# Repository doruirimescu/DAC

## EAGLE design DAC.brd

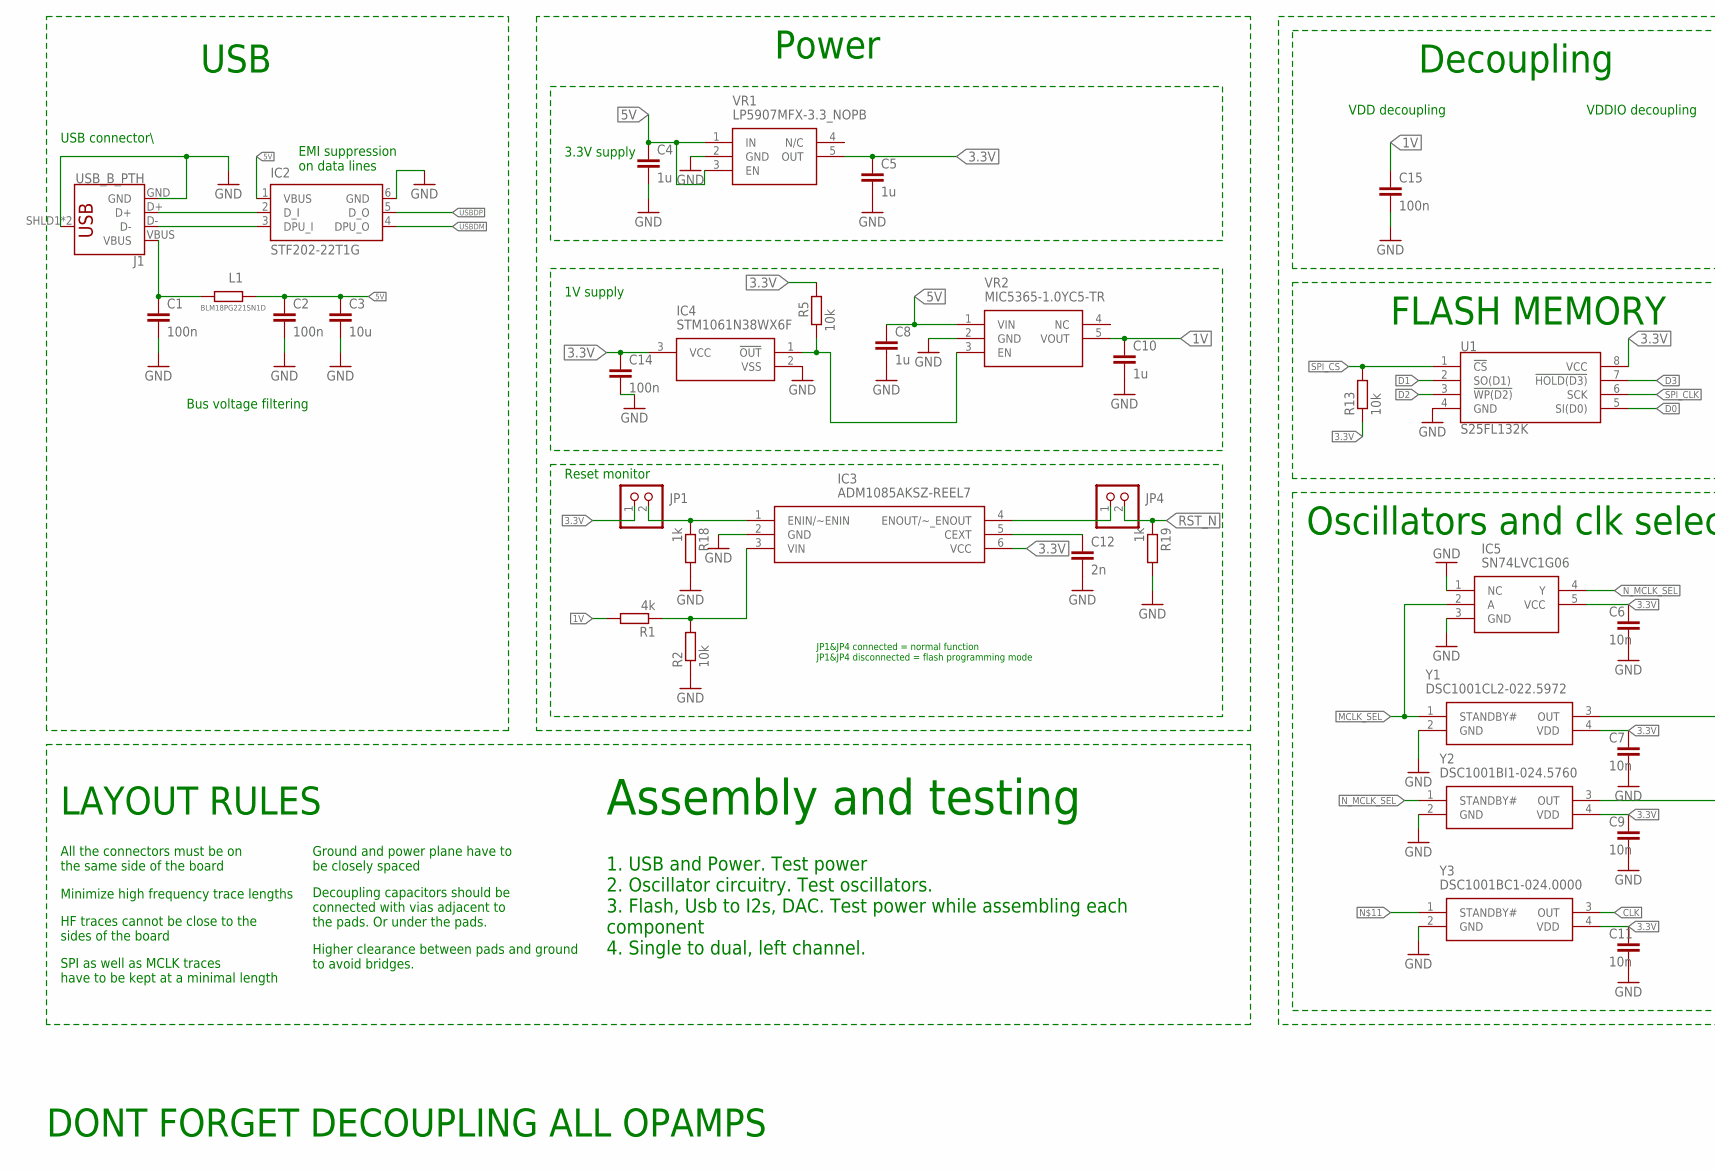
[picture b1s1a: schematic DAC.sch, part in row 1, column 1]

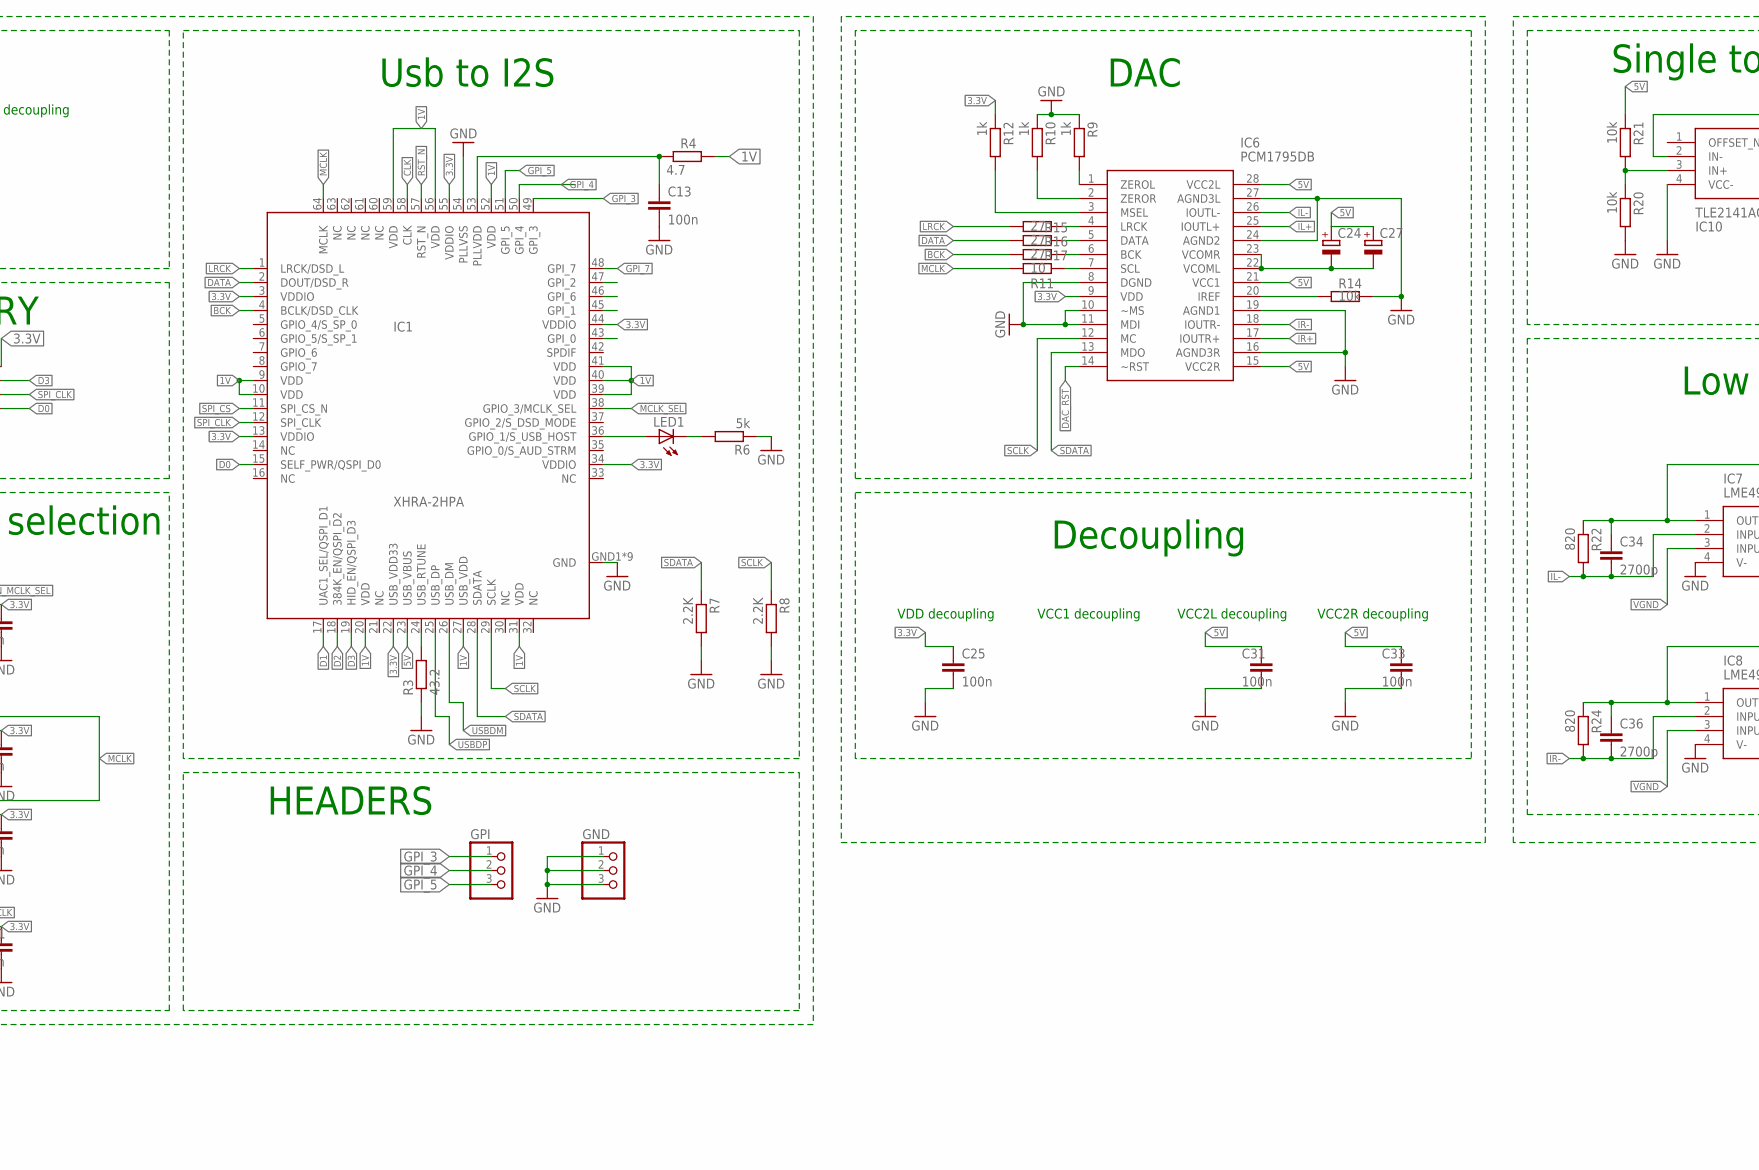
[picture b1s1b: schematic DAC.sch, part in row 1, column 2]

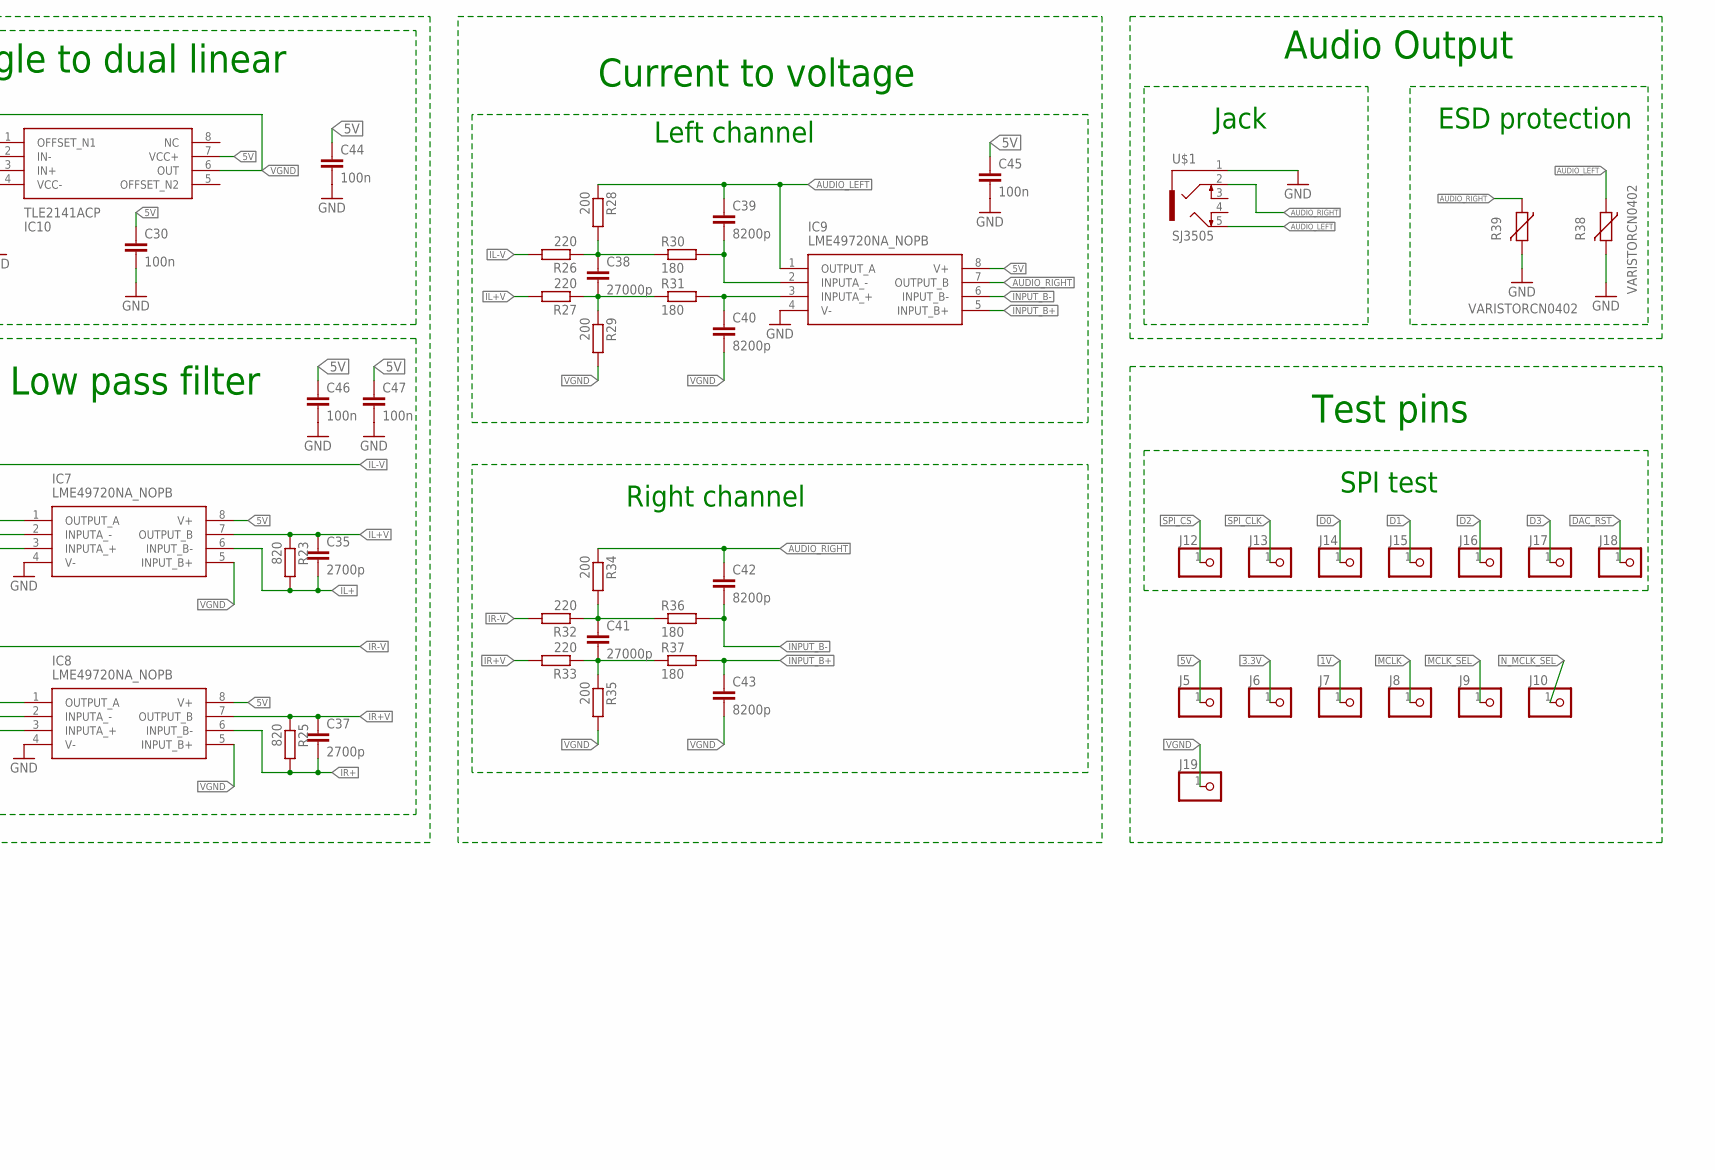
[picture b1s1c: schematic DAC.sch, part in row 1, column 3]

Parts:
C1, C2, C13, C14, C15, C25, C30, C31, C33, C44, C45, C46, C47: 100n; C0603K; MPN A104M15X7RF5TAA
C3: 10u; C0603K
C4, C5, C8, C10: 1u; C0603K
C6, C7, C9, C11: 10n; C0603K
C12: 2n; C0603K
C24, C27: CPOL-EUSANYO_SMD_B6; SANYO-OSCON_SMD_B6
C34, C35, C36, C37: 2700p; C0805
C38, C41: 27000p; C1210
C39, C40, C42, C43: 8200p; C0805
GND: PINHD-1X3; 1X03
GPI: PINHD-1X3; 1X03
IC1: XHRA-2HPA; TQFP64
IC2: STF202-22T1G; SOT23-6
IC3: ADM1085AKSZ-REEL7; SOT65P210X110-6N
IC4: STM1061N38WX6F; SOT103P237X112-3N
IC5: SN74LVC1G06; SOT95P280X145-5N
IC6: PCM1795DB; SOP65P780X200-28N
IC7, IC8, IC9: LME49720NA_NOPB; DIP794W53P254L959H508Q8N
IC10: TLE2141ACP; DIP794W53P254L959H508Q8N
J1: USB_B_PTH; USB-B-PTH
J5, J6, J7, J8, J9, J10, J12, J13, J14, J15, J16, J17, J18, J19: PINHD-1X1; 1X01
JP1, JP4: PINHD-1X2; 1X02
L1: BLM18PG221SN1D; R0603
LED1: LEDSML0603; SML0603
R1: 4k; R0603
R2, R5, R13, R14, R20, R21: 10k; R0603
R3: 43.2; R0603
R4: 4.7; R0603
R6: 5k; R0603
R7, R8: 2.2K; R0603
R9, R10, R12, R18, R19: 1k; R0603
R11: 10; R0603
R15, R16, R17: 27; R0603
R22, R23, R24, R25: 820; R0603
R26, R27, R32, R33: 220; R0603
R28, R29, R34, R35: 200; R0603
R30, R31, R36, R37: 180; R0603
R38, R39: VARISTORCN0402; CT/CN0402
U1: S25FL132K; SO08
U$1: SJ3505
VR1: LP5907MFX-3.3_NOPB; SOT95P280X145-5N
VR2: MIC5365-1.0YC5-TR; SOT65P210X110-5N
Y1: DSC1001CL2-022.5972; DSC1001DL50250000T
Y2: DSC1001BI1-024.5760; DSC1001DL50250000T
Y3: DSC1001BC1-024.0000; DSC1001DL50250000T

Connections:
1V: C10.1, C15.1, IC1.9 (VDD), IC1.10 (VDD), IC1.20 (VDD), IC1.27 (USB_VDD), IC1.31 (VDD), IC1.39 (VDD), IC1.40 (VDD), IC1.41 (VDD), IC1.52 (VDD), IC1.56 (VDD), IC1.59 (VDD), J7.1, R1.2, R4.2, VR2.5 (VOUT)
3.3V: C5.1, C6.1, C7.1, C9.1, C11.1, C14.1, C25.1, IC1.3 (VDDIO), IC1.13 (VDDIO), IC1.22 (USB_VDD33), IC1.34 (VDDIO), IC1.44 (VDDIO), IC1.55 (VDDIO), IC3.6 (VCC), IC4.3 (VCC), IC5.5 (VCC), IC6.9 (VDD), J6.1, JP1.1, R5.2, R12.1, R13.1, U1.8 (VCC), VR1.5 (OUT), Y1.4 (VDD), Y2.4 (VDD), Y3.4 (VDD)
5V: C2.1, C3.1, C4.1, C8.1, C24.+, C27.+, C30.1, C31.1, C33.1, C44.1, C45.1, C46.1, C47.1, IC1.23 (USB_VBUS), IC2.1 (VBUS), IC6.15 (VCC2R), IC6.21 (VCC1), IC6.28 (VCC2L), IC7.8 (V+), IC8.8 (V+), IC9.8 (V+), IC10.7 (VCC+), J5.1, L1.2, R21.1, VR1.1 (IN), VR1.3 (EN), VR2.1 (VIN)
AUDIO_LEFT: C39.1, IC9.1 (OUTPUT_A), R28.1, R38.1, U$1.5
AUDIO_RIGHT: C42.1, IC9.7 (OUTPUT_B), R34.1, R39.1, U$1.2
BCK: IC1.4 (BCLK/DSD_CLK), R17.1
CLK: IC1.58 (CLK), Y3.3 (OUT)
D0: IC1.15 (SELF_PWR/QSPI_D0), J14.1, U1.5 (SI(D0))
D1: IC1.17 (UAC1_SEL/QSPI_D1), J15.1, U1.2 (SO(D1))
D2: IC1.18 (384K_EN/QSPI_D2), J16.1, U1.3 (!WP(D2))
D3: IC1.19 (HID_EN/QSPI_D3), J17.1, U1.7 (!HOLD(D3))
DAC_RST: IC6.14 (~RST), J18.1
DATA: IC1.2 (DOUT/DSD_R), R16.1
DM_I: IC2.3 (DPU_I), J1.D-
DP_I: IC2.2 (D_I), J1.D+
GND: C1.2, C2.2, C3.2, C4.2, C5.2, C6.2, C7.2, C8.2, C9.2, C10.2, C11.2, C12.2, C13.2, C14.2, C15.2, C25.2, C30.2, C31.2, C33.2, C44.2, C45.2, C46.2, C47.2, GND.1, GND.2, GND.3, IC1.54 (PLLVSS), IC1.GND1 (GND), IC1.GND2 (GND), IC1.GND3 (GND), IC1.GND4 (GND), IC1.GND5 (GND), IC1.GND6 (GND), IC1.GND7 (GND), IC1.GND8 (GND), IC1.GND9 (GND), IC2.6 (GND), IC3.2 (GND), IC4.2 (VSS), IC5.1 (NC), IC5.3 (GND), IC6.8 (DGND), IC6.10 (~MS), IC6.11 (MDI), IC6.16 (AGND3R), IC6.19 (AGND1), IC6.24 (AGND2), IC6.27 (AGND3L), IC7.4 (V-), IC8.4 (V-), IC9.4 (V-), IC10.4 (VCC-), J1.GND, J1.SHLD1 (SHIELD), J1.SHLD2 (SHIELD), R2.1, R3.1, R6.1, R7.2, R8.2, R9.1, R10.1, R14.1, R18.2, R19.2, R20.2, R38.2, R39.2, U1.4 (GND), U$1.1, VR1.2 (GND), VR2.2 (GND), Y1.2 (GND), Y2.2 (GND), Y3.2 (GND)
GPI_0: IC1.43 (GPI_0)
GPI_1: IC1.45 (GPI_1)
GPI_2: IC1.47 (GPI_2)
GPI_3: GPI.1, IC1.49 (GPI_3)
GPI_4: GPI.2, IC1.50 (GPI_4)
GPI_5: GPI.3, IC1.51 (GPI_5)
GPI_6: IC1.46 (GPI_6)
GPI_7: IC1.48 (GPI_7)
IL+: C35.2, IC6.25 (IOUTL+), IC7.6 (INPUT_B-), R23.2
IL+V: C35.1, IC7.7 (OUTPUT_B), R23.1, R27.2
IL-: C34.2, IC6.26 (IOUTL-), IC7.2 (INPUTA_-), R22.2
IL-V: C34.1, IC7.1 (OUTPUT_A), R22.1, R26.2
INPUT_B+: C43.1, IC9.5 (INPUT_B+), R37.2
INPUT_B-: C42.2, IC9.6 (INPUT_B-), R36.2
IR+: C37.2, IC6.17 (IOUTR+), IC8.6 (INPUT_B-), R25.2
IR+V: C37.1, IC8.7 (OUTPUT_B), R25.1, R33.2
IR-: C36.2, IC6.18 (IOUTR-), IC8.2 (INPUTA_-), R24.2
IR-V: C36.1, IC8.1 (OUTPUT_A), R24.1, R32.2
LRCK: IC1.1 (LRCK/DSD_L), R15.1
MCLK: IC1.64 (MCLK), J8.1, R11.2, Y1.3 (OUT), Y2.3 (OUT)
MCLK_SEL: IC1.38 (GPIO_3/MCLK_SEL), IC5.2 (A), J9.1, Y1.1 (STANDBY#)
unnamed: C1.1, J1.VBUS, L1.1
unnamed: C12.1, IC3.5 (CEXT)
unnamed: IC3.3 (VIN), R1.1, R2.2
unnamed: IC1.24 (USB_RTUNE), R3.2
unnamed: C13.1, IC1.53 (PLLVDD), R4.1
unnamed: IC4.1 (!OUT), R5.1, VR2.3 (EN)
unnamed: IC1.36 (GPIO_1/S_USB_HOST), LED1.A
unnamed: LED1.C, R6.2
unnamed: IC6.1 (ZEROL), R9.2
unnamed: IC6.7 (SCL), R11.1
unnamed: IC6.2 (ZEROR), R10.2
unnamed: IC6.3 (MSEL), R12.2
unnamed: IC6.20 (IREF), R14.2
unnamed: IC6.4 (LRCK), R15.2
unnamed: IC6.6 (BCK), R17.2
unnamed: IC6.5 (DATA), R16.2
unnamed: IC3.1 (ENIN/~ENIN), JP1.2, R18.1
unnamed: IC3.4 (ENOUT/~_ENOUT), JP4.1
unnamed: C24.-, C27.-, IC6.22 (VCOML), IC6.23 (VCOMR)
unnamed: IC10.3 (IN+), R20.1, R21.2
unnamed: C38.1, R26.1, R28.2, R30.1
unnamed: C38.2, R27.1, R29.1, R31.1
unnamed: C40.1, IC9.3 (INPUTA_+), R31.2
unnamed: C39.2, IC9.2 (INPUTA_-), R30.2
unnamed: C41.1, R32.1, R34.2, R36.1
unnamed: C41.2, R33.1, R35.1, R37.1
N_MCLK_SEL: IC5.4 (Y), J10.1, Y2.1 (STANDBY#)
RST_N: IC1.57 (RST_N), JP4.2, R19.1
SCLK: IC1.29 (SCLK), IC6.12 (MC), R8.1
SDATA: IC1.28 (SDATA), IC6.13 (MDO), R7.1
SPI_CLK: IC1.12 (SPI_CLK), J13.1, U1.6 (SCK)
SPI_CS: IC1.11 (SPI_CS_N), J12.1, R13.2, U1.1 (!CS)
USBDM: IC1.26 (USB_DM), IC2.4 (DPU_O)
USBDP: IC1.25 (USB_DP), IC2.5 (D_O)
VGND: C40.2, C43.2, IC7.3 (INPUTA_+), IC7.5 (INPUT_B+), IC8.3 (INPUTA_+), IC8.5 (INPUT_B+), IC10.2 (IN-), IC10.6 (OUT), J19.1, R29.2, R35.2

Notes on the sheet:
USB
EMI suppression on data lines
USB connector\
Bus voltage filtering
Power
3.3V supply
1V supply
Reset monitor
VDD decoupling
VDDIO decoupling
FLASH MEMORY
Oscillators and clk selection
HEADERS
DAC
LAYOUT RULES
All the connectors must be on the same side of the board
Minimize high frequency trace lengths
HF traces cannot be close to the sides of the board
SPI as well as MCLK traces have to be kept at a minimal length
Ground and power plane have to be closely spaced
Decoupling capacitors should be connected with vias adjacent to the pads. Or under the pads.
VCC2L decoupling
VCC1 decoupling
VCC2R decoupling
JP1&JP4 connected = normal function JP1&JP4 disconnected = flash programming mode
Decoupling
Usb to I2S
Single to dual linear
Low pass filter
Current to voltage
Assembly and testing
1. USB and Power. Test power 2. Oscillator circuitry. Test oscillators. 3. Flash, Usb to I2s, DAC. Test power while assembling each component 4. Single to dual, left channel.
Audio Output
Test pins
Higher clearance between pads and ground to avoid bridges.
Right channel
Left channel
ESD protection
Jack
SPI test

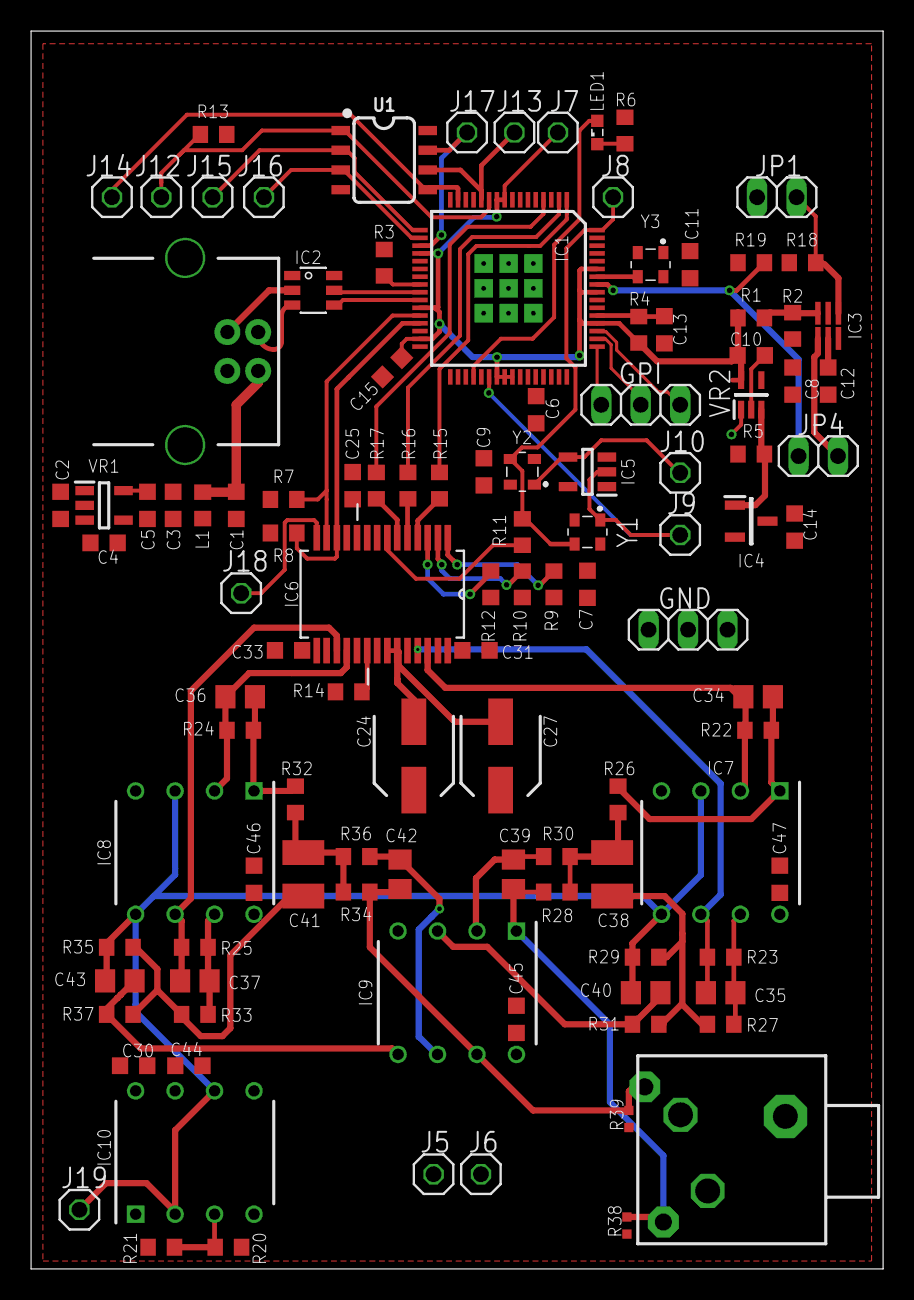
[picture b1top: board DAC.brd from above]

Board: 4 copper layers, 54.8 x 79.7 mm, 112 parts (0 on the bottom side), 67 nets.

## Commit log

2019-06-06 Add initial project
2019-08-07 Add layout progress
2019-08-07 Add more layout progress
2021-08-09 Remove backups

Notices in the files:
parts and their libraries:
SparkFun-Connectors: Licensing: Creative Commons ShareAlike 4.0 International - https://creativecommons.org/licenses/by-sa/4.0
